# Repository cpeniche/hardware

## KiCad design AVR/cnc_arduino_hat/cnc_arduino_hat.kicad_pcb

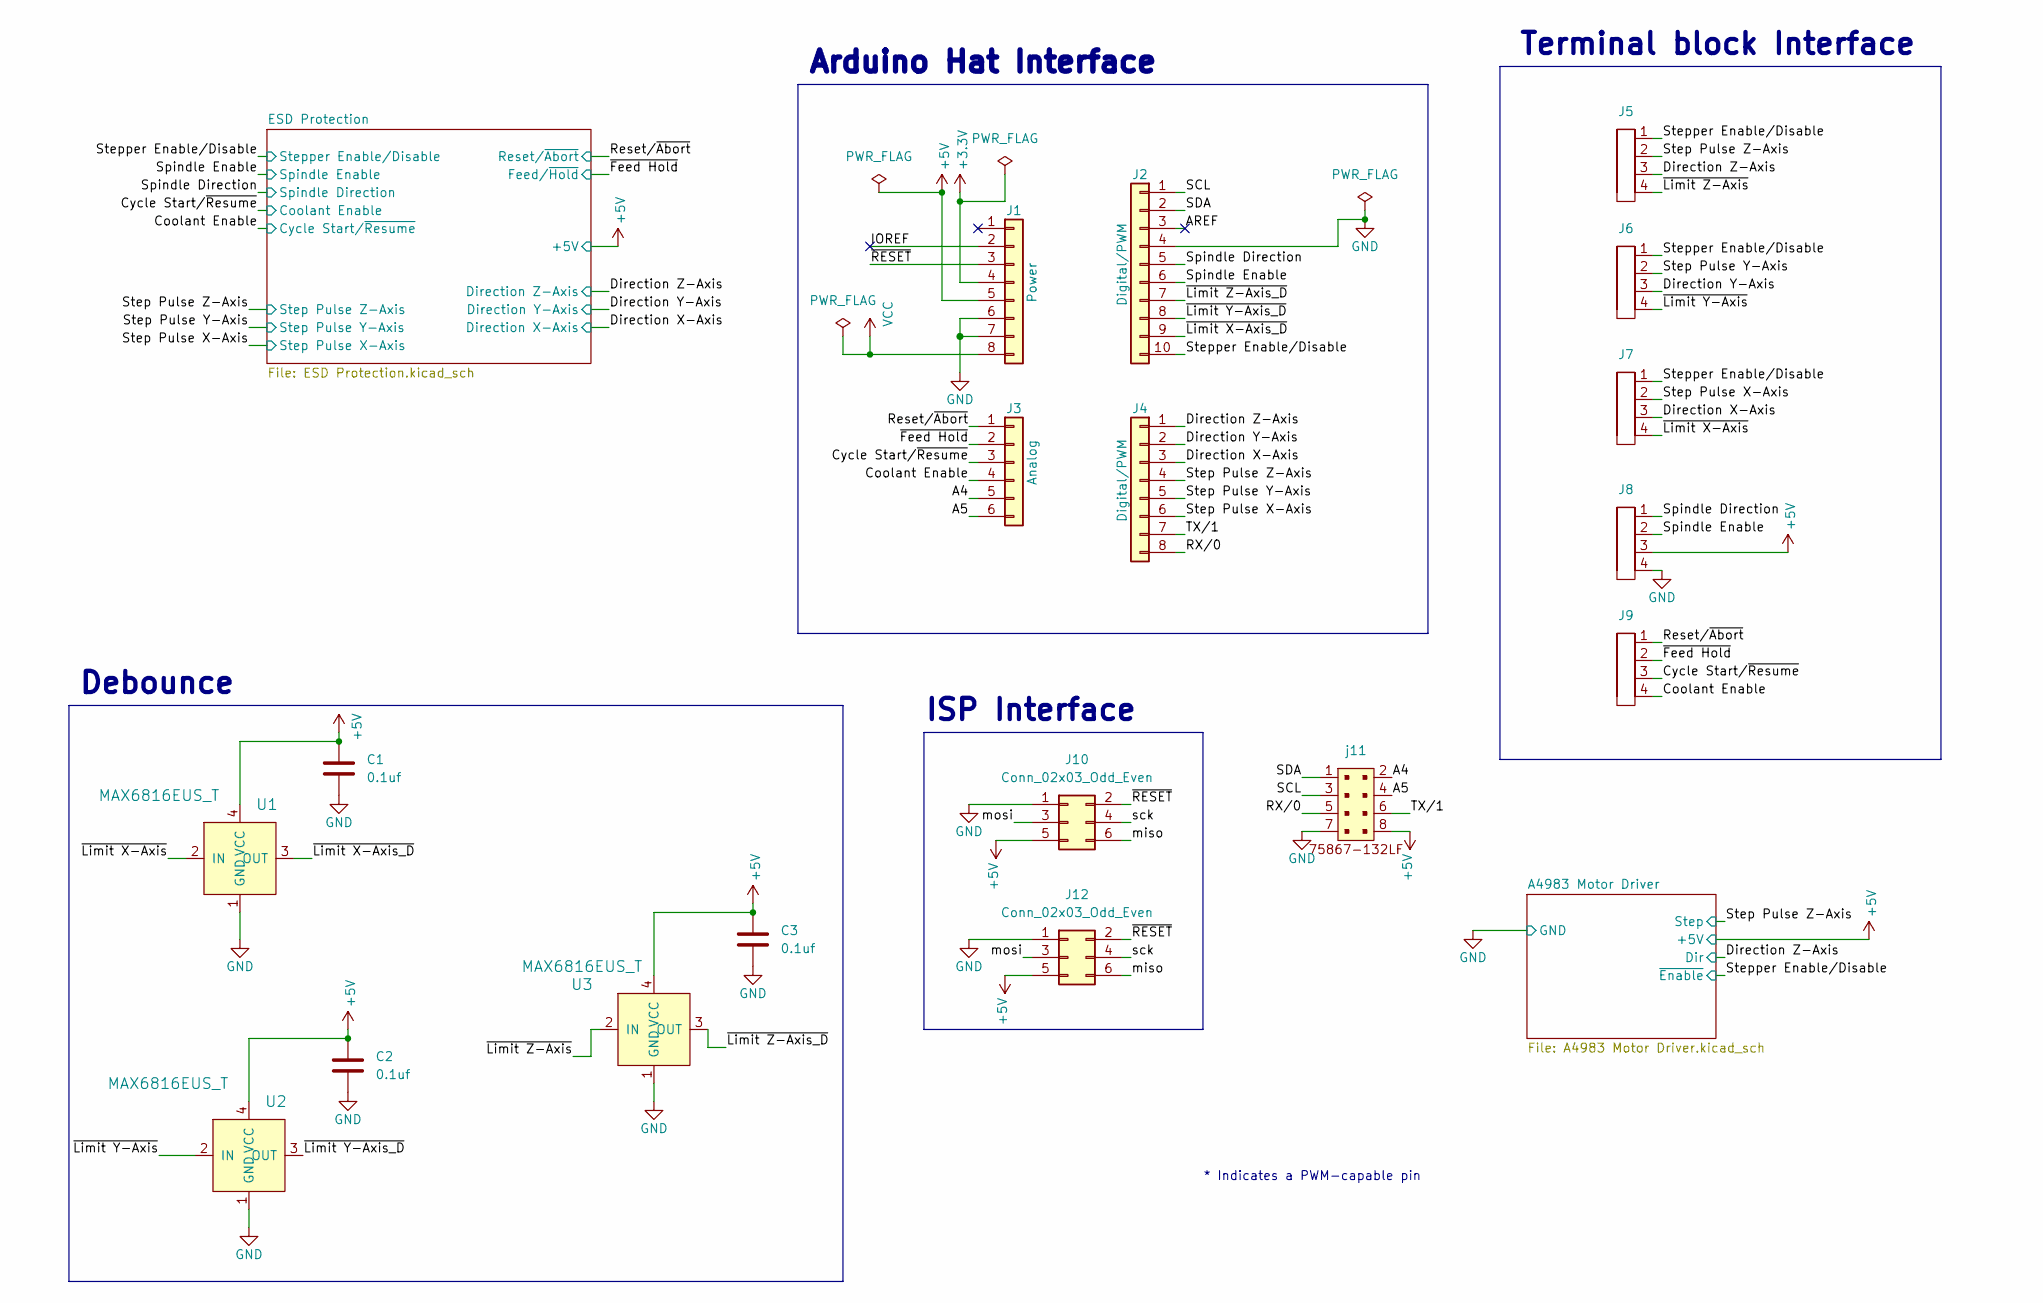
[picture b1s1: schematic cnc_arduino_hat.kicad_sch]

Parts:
C1, C2, C3: 0.1uf; C_0603_1608Metric_Pad1.08x0.95mm_HandSolder
J1: Power; PinHeader_1x08_P2.54mm_Vertical_SMD_Pin1Left
J2: Digital/PWM; PinHeader_1x10_P2.54mm_Vertical_SMD_Pin1Right
J3: Analog; PinHeader_1x06_P2.54mm_Vertical_SMD_Pin1Left
J4: Digital/PWM; PinHeader_1x08_P2.54mm_Vertical_SMD_Pin1Left
J5, J6, J7, J8, J9: Term_Block_1X4_P3.18mm
J10: Conn_02x03_Odd_Even; PinSocket_2x03_P2.54mm_Vertical
J12: Conn_02x03_Odd_Even; PinHeader_2x03_P2.54mm_Vertical
U1, U2, U3: MAX6816EUS_T; SOT-143-4; MPN MAX6816EUS+T; Digi-Key_PN MAX6816EUS+TCT-ND
j11: PinHeader_2x4_P2.54mm_Shrouded

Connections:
+3V3: J1.4
+5V: C1.1, C2.1, C3.1, J1.5, J8.3, J10.5, J12.5, U1.4 (VCC), U2.4 (VCC), U3.4 (VCC), j11.8; also elsewhere on the board
/A4: J3.5, j11.2
/A5: J3.6, j11.4
/AREF: J2.3
/Coolant Enable: J3.4, J9.4; also elsewhere on the board
/Cycle Start/~Resume: J3.3, J9.3; also elsewhere on the board
/Direction X-Axis: J4.3, J7.3; also elsewhere on the board
/Direction Y-Axis: J4.2, J6.3; also elsewhere on the board
/Direction Z-Axis: J4.1, J5.3; also elsewhere on the board
/IOREF: J1.2
/RX/0: J4.8, j11.5
/Reset/~Abort: J3.1, J9.1; also elsewhere on the board
/SCL: J2.1, j11.3
/SDA: J2.2, j11.1
/Spindle Direction: J2.5, J8.1; also elsewhere on the board
/Spindle Enable: J2.6, J8.2; also elsewhere on the board
/Step Pulse X-Axis: J4.6, J7.2; also elsewhere on the board
/Step Pulse Y-Axis: J4.5, J6.2; also elsewhere on the board
/Step Pulse Z-Axis: J4.4, J5.2; also elsewhere on the board
/Stepper Enable/Disable: J2.10, J5.1, J6.1, J7.1; also elsewhere on the board
/TX/1: J4.7, j11.6
/miso: J10.6, J12.6
/mosi: J10.3, J12.3
/sck: J10.4, J12.4
/~Feed Hold: J3.2, J9.2; also elsewhere on the board
/~Limit X-Axis_D: J2.9, U1.3 (OUT)
/~Limit X-Axis: J7.4, U1.2 (IN)
/~Limit Y-Axis_D: J2.8, U2.3 (OUT)
/~Limit Y-Axis: J6.4, U2.2 (IN)
/~Limit Z-Axis_D: J2.7, U3.3 (OUT)
/~Limit Z-Axis: J5.4, U3.2 (IN)
/~RESET: J1.3, J10.2, J12.2
GND: C1.2, C2.2, C3.2, J1.6, J1.7, J2.4, J8.4, J10.1, J12.1, U1.1 (GND), U2.1 (GND), U3.1 (GND), j11.7; also elsewhere on the board
VCC: J1.8

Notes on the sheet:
ISP Interface
Terminal block Interface
Debounce
* Indicates a PWM-capable pin
Arduino Hat Interface

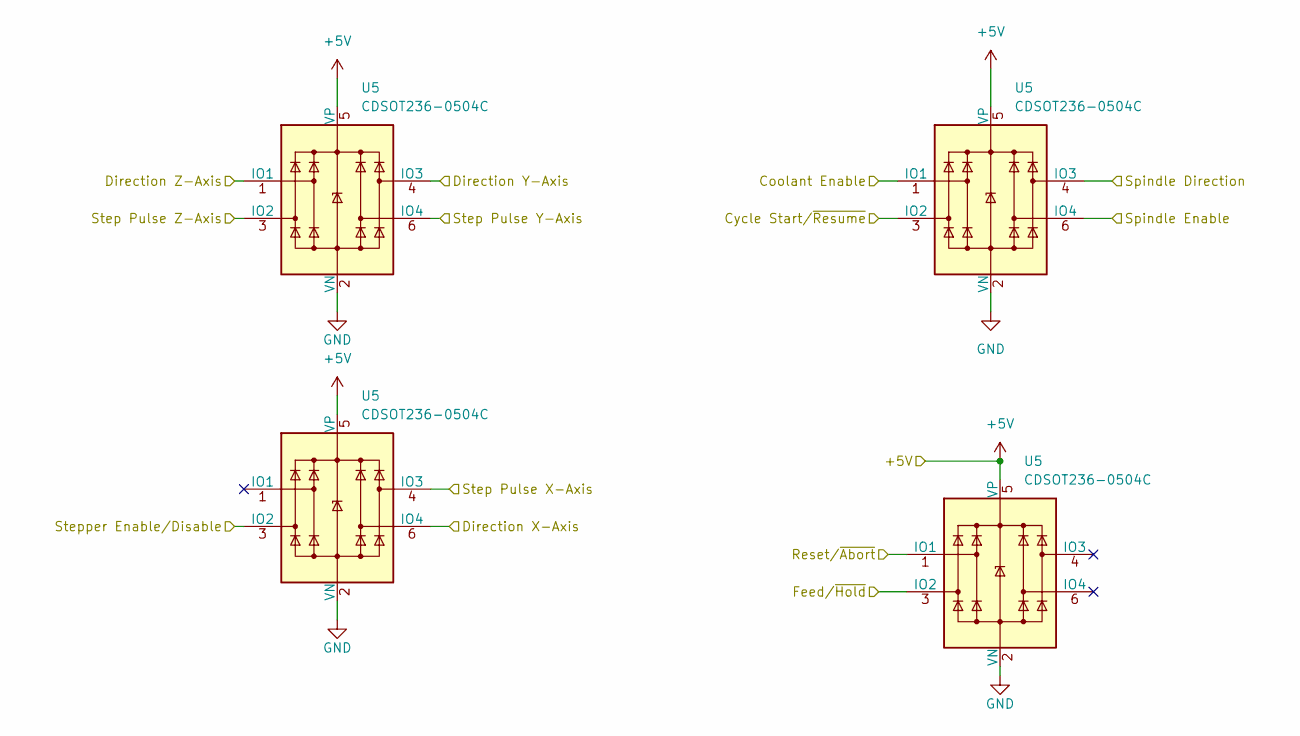
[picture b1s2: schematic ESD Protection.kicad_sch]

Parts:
U5: CDSOT236-0504C; SOT-23-6

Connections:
+5V: U5.5 (VP); also elsewhere on the board
/Direction Y-Axis: U5.4 (IO3); also elsewhere on the board
/Direction Z-Axis: U5.1 (IO1); also elsewhere on the board
/Step Pulse Y-Axis: U5.6 (IO4); also elsewhere on the board
/Step Pulse Z-Axis: U5.3 (IO2); also elsewhere on the board
GND: U5.2 (VN); also elsewhere on the board

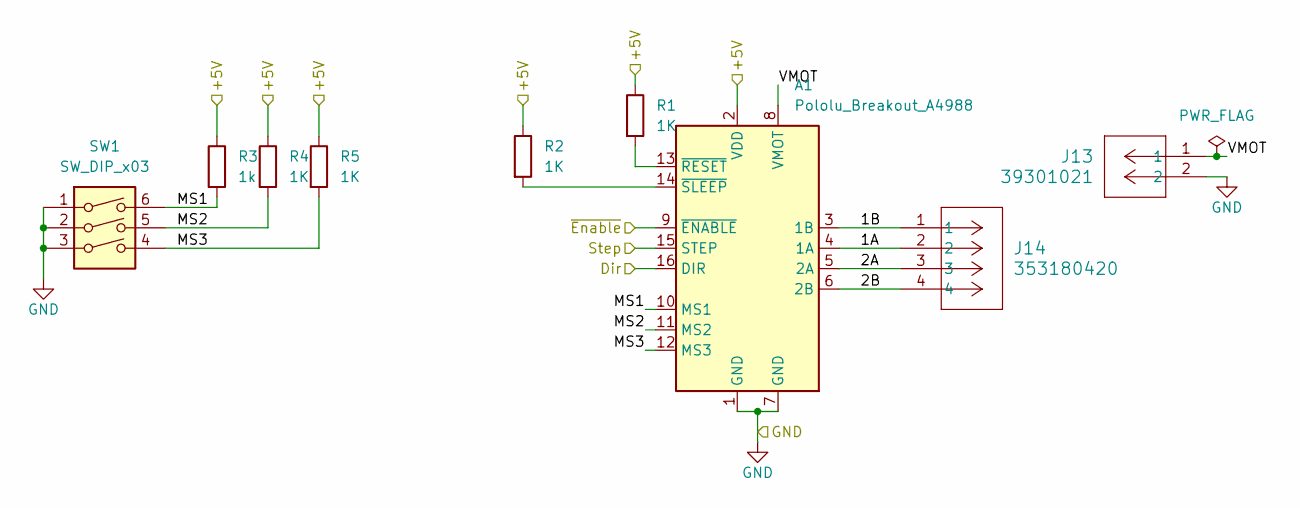
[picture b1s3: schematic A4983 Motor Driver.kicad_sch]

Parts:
A1: Pololu_Breakout_A4988; Pololu_Breakout-16_15.2x20.3mm
J13: 39301021; CON_39301021
J14: 353180420; CONN_35318-0420_MOL
R1, R2, R4, R5: 1K; R_0805_2012Metric_Pad1.20x1.40mm_HandSolder
R3: 1k; R_0805_2012Metric_Pad1.20x1.40mm_HandSolder
SW1: SW_DIP_x03; SW_DIP_SPSTx03_Slide_9.78x9.8mm_W8.61mm_P2.54mm

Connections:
+5V: A1.2 (VDD), R1.1, R2.1, R3.1, R4.1, R5.1; also elsewhere on the board
/A4983 Motor Driver/1A: A1.4 (1A), J14.2
/A4983 Motor Driver/1B: A1.3 (1B), J14.1
/A4983 Motor Driver/2A: A1.5 (2A), J14.3
/A4983 Motor Driver/2B: A1.6 (2B), J14.4
/A4983 Motor Driver/MS1: A1.10 (MS1), R3.2, SW1.6
/A4983 Motor Driver/MS2: A1.11 (MS2), R4.2, SW1.5
/A4983 Motor Driver/MS3: A1.12 (MS3), R5.2, SW1.4
/A4983 Motor Driver/VMOT: A1.8 (VMOT), J13.1
/Direction Z-Axis: A1.16 (DIR); also elsewhere on the board
/Step Pulse Z-Axis: A1.15 (STEP); also elsewhere on the board
/Stepper Enable/Disable: A1.9 (~ENABLE); also elsewhere on the board
GND: A1.1 (GND), A1.7 (GND), J13.2, SW1.1, SW1.2, SW1.3; also elsewhere on the board
unnamed: A1.13 (~RESET), R1.2
unnamed: A1.14 (~SLEEP), R2.2

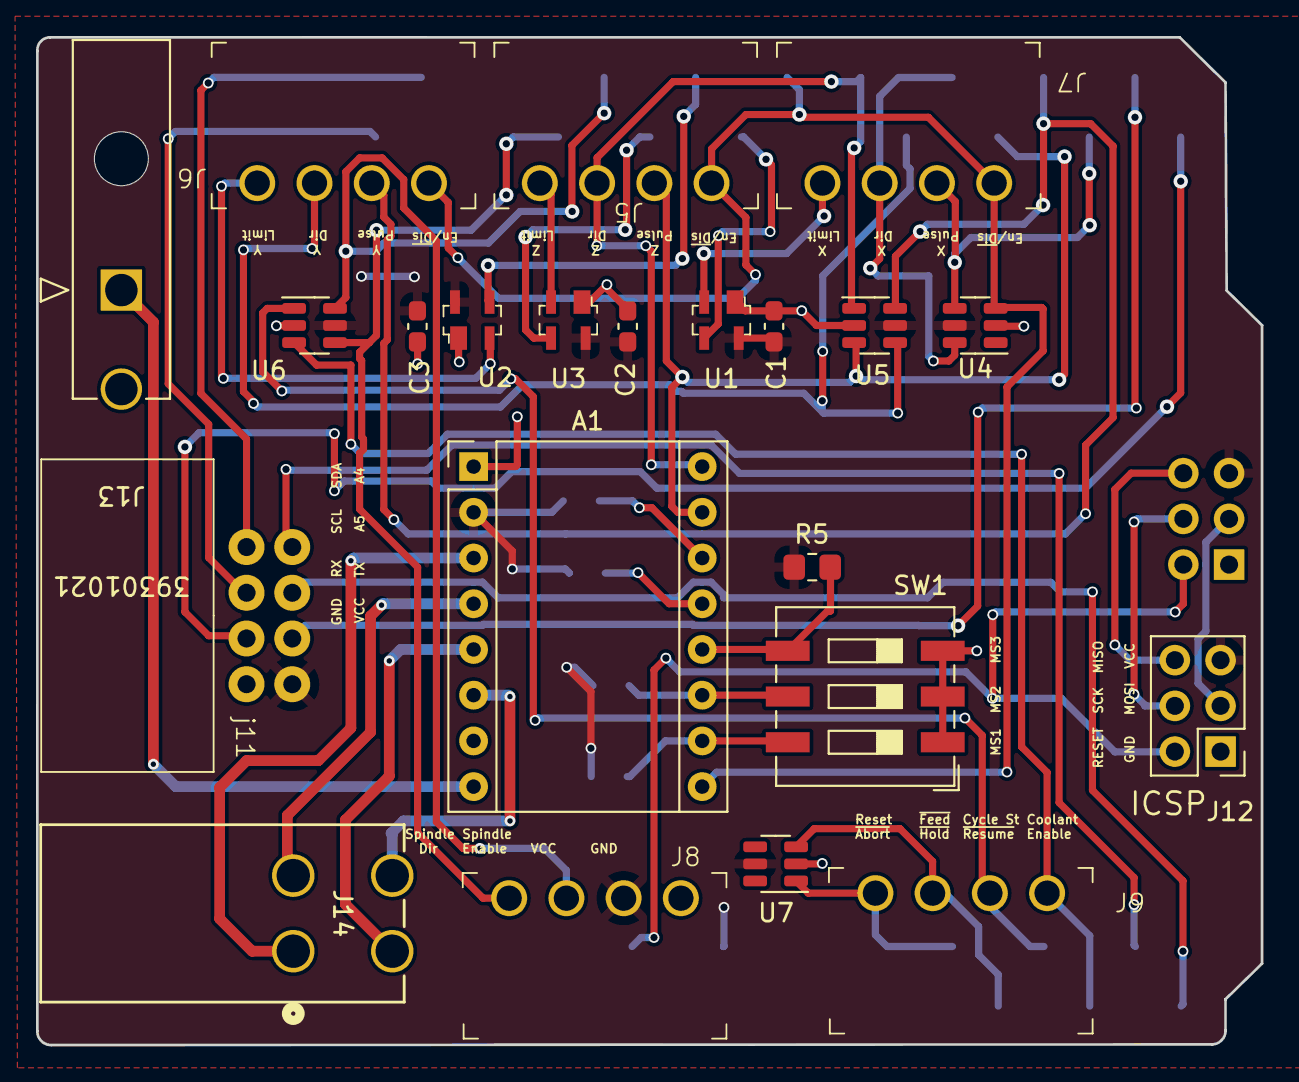
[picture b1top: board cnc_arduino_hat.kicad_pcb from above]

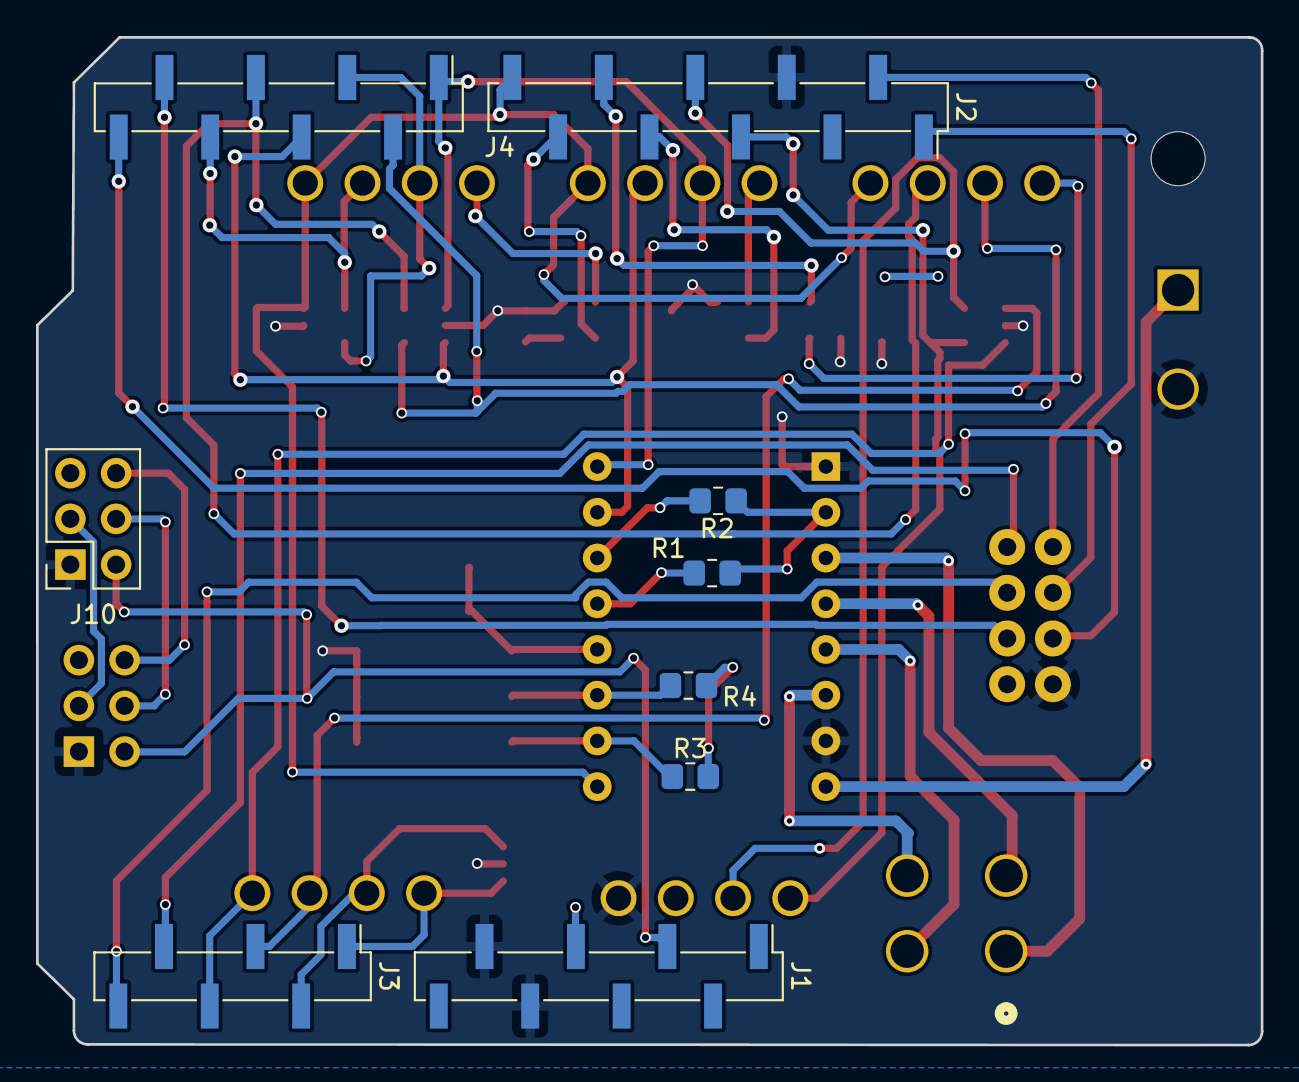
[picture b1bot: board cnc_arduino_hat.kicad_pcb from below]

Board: 2 copper layers, 68.0 x 56.0 mm, 31 parts (9 on the bottom side), 41 nets.

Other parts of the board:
U4, U6, U7: CDSOT236-0504C; SOT-23-6

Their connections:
+5V: U4.5 (VP), U6.5 (VP), U7.5 (VP); also elsewhere on the board
/Coolant Enable: U6.3 (IO2); also elsewhere on the board
/Cycle Start/~Resume: U6.1 (IO1); also elsewhere on the board
/Direction X-Axis: U4.6 (IO4); also elsewhere on the board
/Reset/~Abort: U7.1 (IO1); also elsewhere on the board
/Spindle Direction: U6.4 (IO3); also elsewhere on the board
/Spindle Enable: U6.6 (IO4); also elsewhere on the board
/Step Pulse X-Axis: U4.4 (IO3); also elsewhere on the board
/Stepper Enable/Disable: U4.3 (IO2); also elsewhere on the board
/~Feed Hold: U7.3 (IO2); also elsewhere on the board
GND: U4.2 (VN), U6.2 (VN), U7.2 (VN); also elsewhere on the board

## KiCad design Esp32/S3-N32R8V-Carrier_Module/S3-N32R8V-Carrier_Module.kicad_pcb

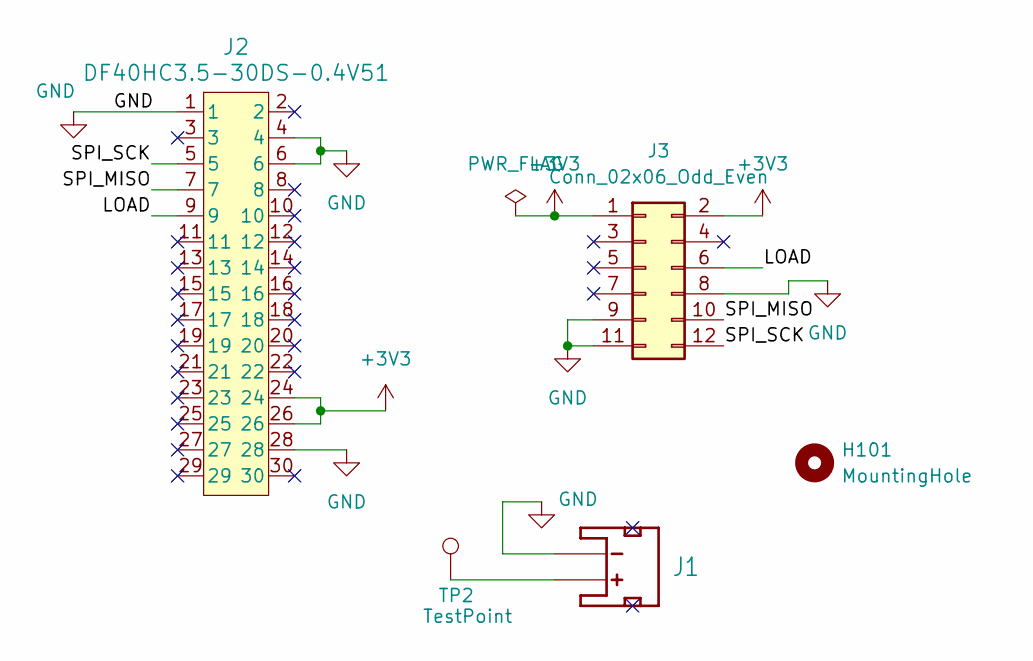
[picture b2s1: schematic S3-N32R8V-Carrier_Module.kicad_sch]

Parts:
H101: MountingHole; MountingHole_2.7mm
J1: JST_PH_S2B-PH-SM4-TB_1x02-1MP_P2.00mm_Horizontal
J2: DF40HC3.5-30DS-0.4V51; CONN_DF40HC3.5-30DS-0.4V51_HIR
J3: Conn_02x06_Odd_Even; PinHeader_2x06_P2.54mm_Vertical_SMD
TP2: TestPoint; TestPoint_Pad_1.0x1.0mm

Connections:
+3V3: J2.24, J2.26, J3.1, J3.2
/LOAD: J2.9, J3.6
/SPI_MISO: J2.7, J3.10
/SPI_SCK: J2.5, J3.12
GND: J1.1 (-), J2.1, J2.4, J2.6, J2.28, J3.8, J3.9, J3.11
unnamed: J1.2 (+), TP2.1

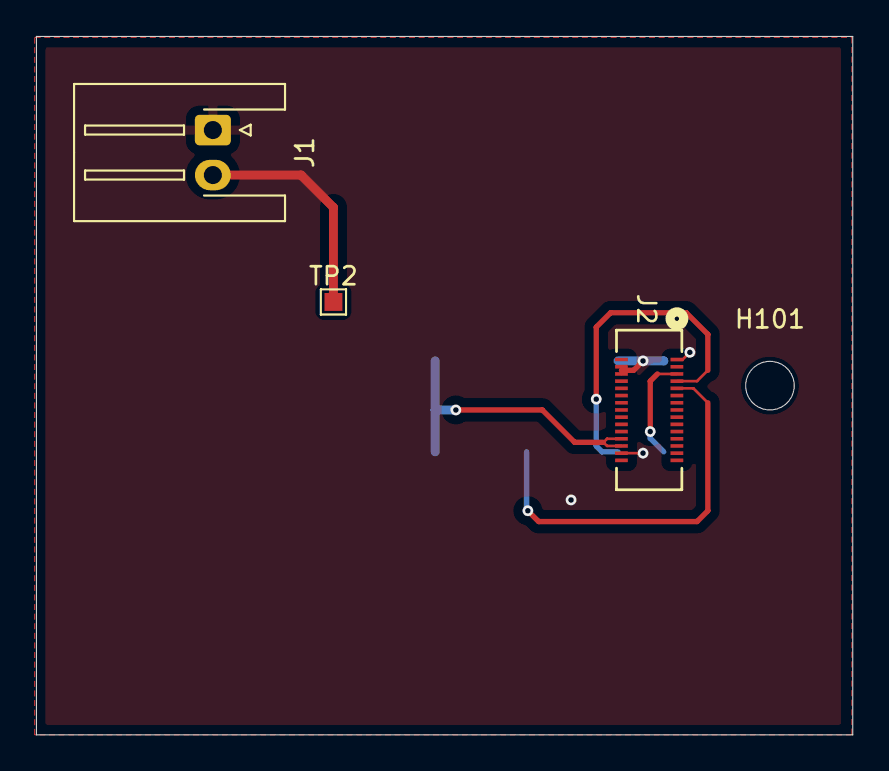
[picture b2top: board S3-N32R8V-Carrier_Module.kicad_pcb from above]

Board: 2 copper layers, 45.3 x 38.8 mm, 5 parts (1 on the bottom side), 6 nets.

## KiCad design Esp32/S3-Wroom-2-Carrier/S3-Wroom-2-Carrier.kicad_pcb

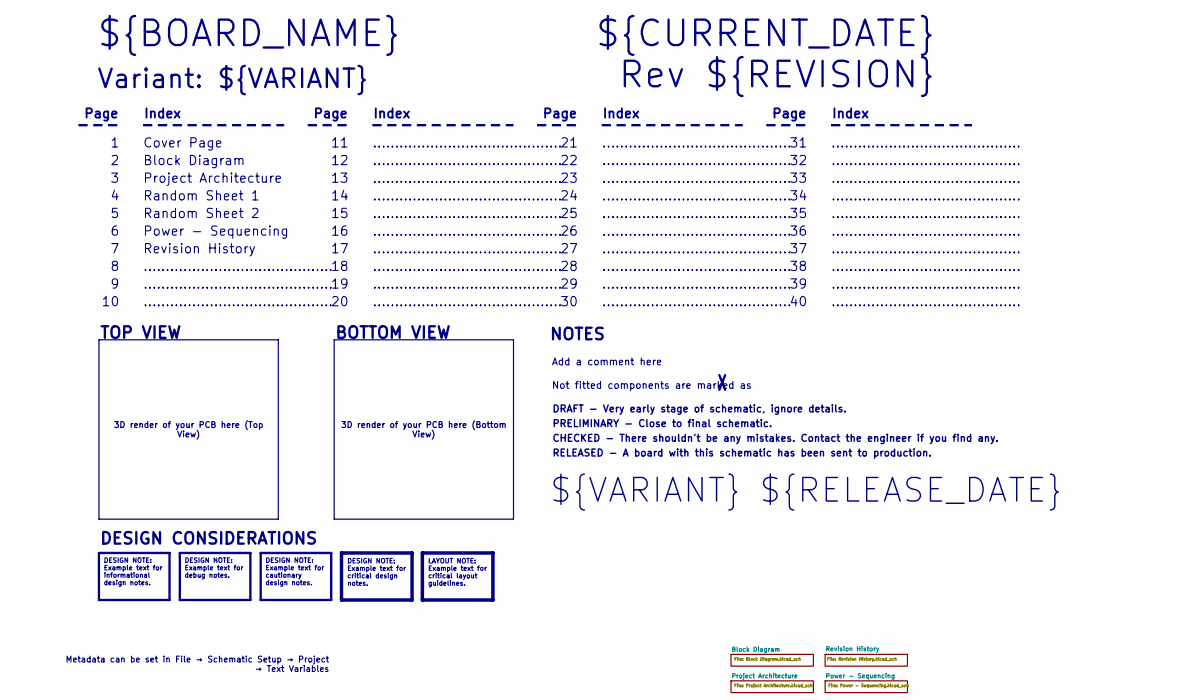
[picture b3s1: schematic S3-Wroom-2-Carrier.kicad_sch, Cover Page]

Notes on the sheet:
BOTTOM VIEW
...........................................
RELEASED - A board with this schematic has been sent to production.
Page
TOP VIEW
Not fitted components are marked as
Index
PRELIMINARY - Close to final schematic.
${VARIANT} ${RELEASE_DATE}
Random Sheet 1
${CURRENT_DATE}
Variant: ${VARIANT}
Rev ${REVISION}
Random Sheet 2
${BOARD_NAME}
DRAFT - Very early stage of schematic, ignore details.
Power - Sequencing
Block Diagram
Add a comment here
Cover Page
NOTES
Project Architecture
CHECKED - There shouldn't be any mistakes. Contact the engineer if you find any.
DESIGN CONSIDERATIONS
Revision History
3D render of your PCB here (Bottom View)
3D render of your PCB here (Top View)
Metadata can be set in File → Schematic Setup → Project → Text Variables
DESIGN NOTE: Example text for informational design notes.
LAYOUT NOTE: Example text for critical layout guidelines.
DESIGN NOTE: Example text for cautionary design notes.
DESIGN NOTE: Example text for debug notes.
DESIGN NOTE: Example text for critical design notes.

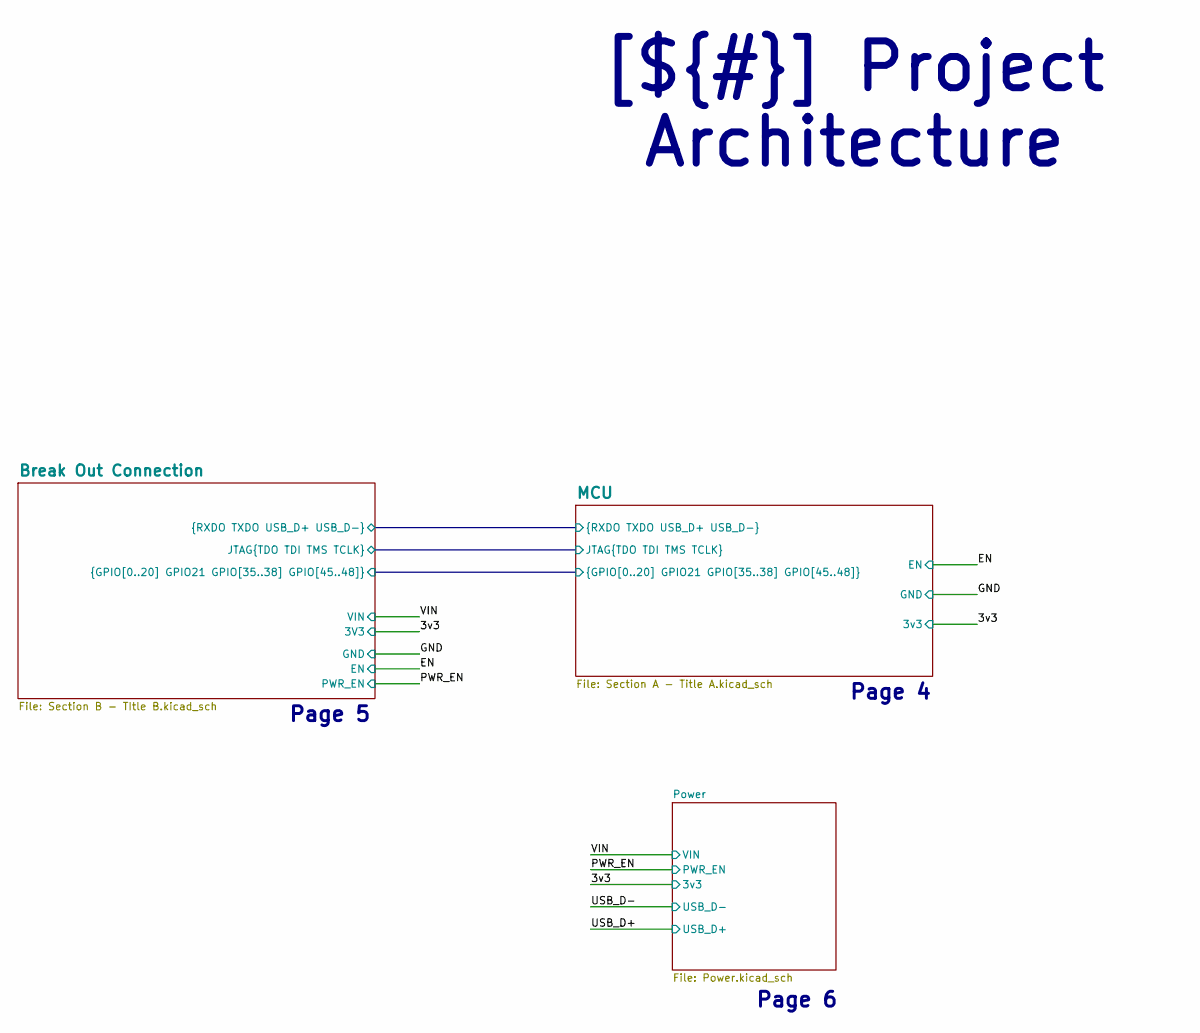
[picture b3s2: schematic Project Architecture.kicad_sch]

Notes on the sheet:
Page 6
Page 4
Page 5
[${#}] ${TITLE}

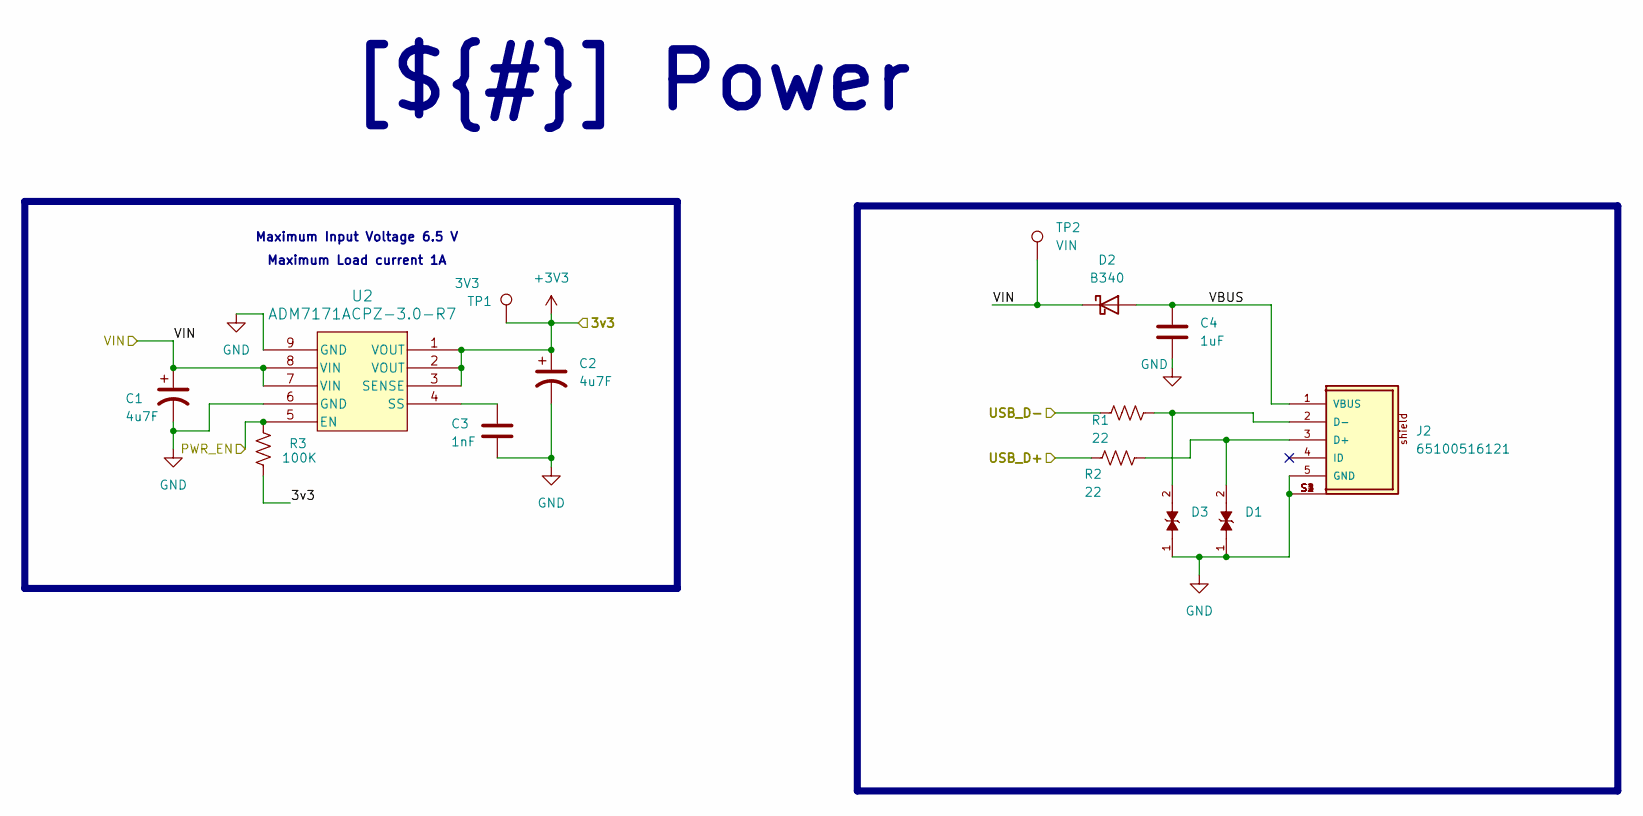
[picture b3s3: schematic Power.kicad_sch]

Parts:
C1, C2: 4u7F; C_0805_2012Metric_Pad1.18x1.45mm_HandSolder
C3: 1nF; C_0805_2012Metric_Pad1.18x1.45mm_HandSolder
C4: 1uF; C_0805_2012Metric_Pad1.18x1.45mm_HandSolder
D1, D3: DIOC1608X36N
D2: B340; D_SMA
J2: 65100516121; Usb_B_mini_Wurth_65100516121
R1, R2: 22; R_0805_2012Metric_Pad1.20x1.40mm_HandSolder
R3: 100K; R_0805_2012Metric_Pad1.20x1.40mm_HandSolder
TP1: 3V3; TestPoint_Pad_1.0x1.0mm
TP2: VIN; TestPoint_Pad_1.0x1.0mm
U2: ADM7171ACPZ-3.0-R7; LFCSP-8-1EP_3x3mm_P0.5mm_EP_1.70x2.54mm

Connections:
+3V3: C2.1, R3.2, TP1.1, U2.1 (VOUT), U2.2 (VOUT), U2.3 (SENSE); also elsewhere on the board
/Project Architecture/Break Out Connection/USB_D+: R2.1; also elsewhere on the board
/Project Architecture/Break Out Connection/USB_D-: R1.1; also elsewhere on the board
/Project Architecture/PWR_EN: R3.1, U2.5 (EN); also elsewhere on the board
/Project Architecture/Power/VBUS: C4.1, D2.2 (A), J2.1 (VBUS)
/Project Architecture/VIN: C1.1, D2.1 (K), TP2.1, U2.7 (VIN), U2.8 (VIN); also elsewhere on the board
GND: C1.2, C2.2, C3.2, C4.2, D1.1, D3.1, J2.5 (GND), J2.S1, J2.S2, J2.S3, J2.S4, U2.6 (GND), U2.9 (GND); also elsewhere on the board
unnamed: D1.2, J2.3 (D+), R2.2
unnamed: D3.2, J2.2 (D-), R1.2
unnamed: C3.1, U2.4 (SS)

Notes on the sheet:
Maximum Load current 1A
Maximum Input Voltage 6.5 V
[${#}] ${TITLE}

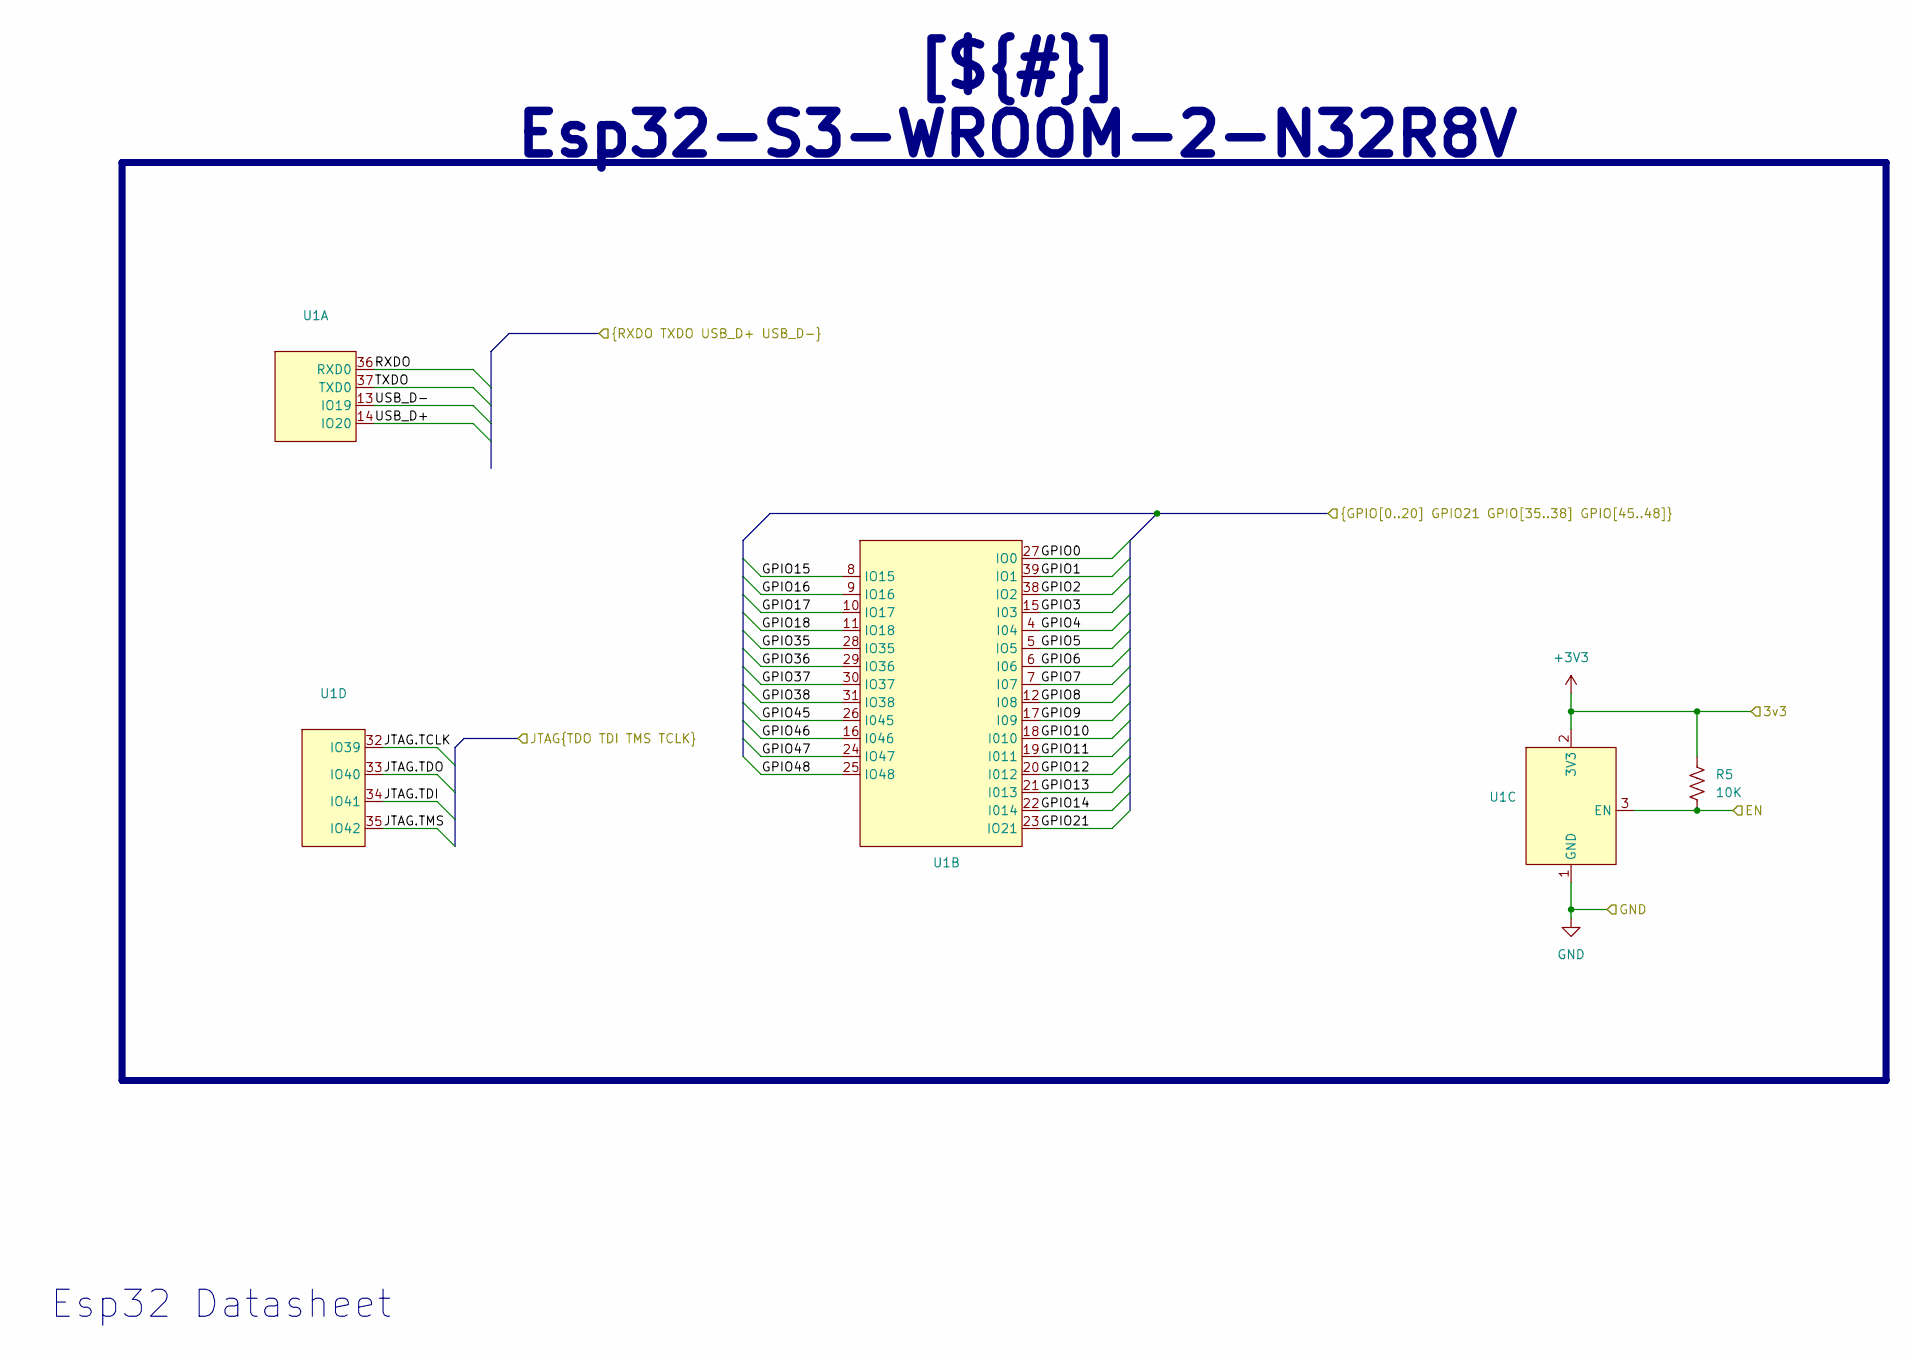
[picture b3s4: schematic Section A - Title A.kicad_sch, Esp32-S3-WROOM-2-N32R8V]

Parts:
R5: 10K; R_0805_2012Metric_Pad1.20x1.40mm_HandSolder
U1: ESP32-S3-WROOM-2

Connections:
+3V3: R5.1, U1.2 (3V3); also elsewhere on the board
/Project Architecture/Break Out Connection/GPIO0: U1.27 (IO0); also elsewhere on the board
/Project Architecture/Break Out Connection/GPIO1: U1.39 (IO1); also elsewhere on the board
/Project Architecture/Break Out Connection/GPIO2: U1.38 (IO2); also elsewhere on the board
/Project Architecture/Break Out Connection/GPIO3: U1.15 (I03); also elsewhere on the board
/Project Architecture/Break Out Connection/GPIO4: U1.4 (I04); also elsewhere on the board
/Project Architecture/Break Out Connection/GPIO5: U1.5 (IO5); also elsewhere on the board
/Project Architecture/Break Out Connection/GPIO6: U1.6 (I06); also elsewhere on the board
/Project Architecture/Break Out Connection/GPIO7: U1.7 (I07); also elsewhere on the board
/Project Architecture/Break Out Connection/GPIO8: U1.12 (I08); also elsewhere on the board
/Project Architecture/Break Out Connection/GPIO9: U1.17 (I09); also elsewhere on the board
/Project Architecture/Break Out Connection/GPIO10: U1.18 (I010); also elsewhere on the board
/Project Architecture/Break Out Connection/GPIO11: U1.19 (I011); also elsewhere on the board
/Project Architecture/Break Out Connection/GPIO12: U1.20 (I012); also elsewhere on the board
/Project Architecture/Break Out Connection/GPIO13: U1.21 (I013); also elsewhere on the board
/Project Architecture/Break Out Connection/GPIO14: U1.22 (I014); also elsewhere on the board
/Project Architecture/Break Out Connection/GPIO15: U1.8 (IO15); also elsewhere on the board
/Project Architecture/Break Out Connection/GPIO16: U1.9 (IO16); also elsewhere on the board
/Project Architecture/Break Out Connection/GPIO17: U1.10 (IO17); also elsewhere on the board
/Project Architecture/Break Out Connection/GPIO18: U1.11 (IO18); also elsewhere on the board
/Project Architecture/Break Out Connection/GPIO21: U1.23 (IO21); also elsewhere on the board
/Project Architecture/Break Out Connection/GPIO35: U1.28 (IO35); also elsewhere on the board
/Project Architecture/Break Out Connection/GPIO36: U1.29 (IO36); also elsewhere on the board
/Project Architecture/Break Out Connection/GPIO37: U1.30 (IO37); also elsewhere on the board
/Project Architecture/Break Out Connection/GPIO38: U1.31 (IO38); also elsewhere on the board
/Project Architecture/Break Out Connection/GPIO45: U1.26 (I045); also elsewhere on the board
/Project Architecture/Break Out Connection/GPIO46: U1.16 (I046); also elsewhere on the board
/Project Architecture/Break Out Connection/GPIO47: U1.24 (IO47); also elsewhere on the board
/Project Architecture/Break Out Connection/GPIO48: U1.25 (IO48); also elsewhere on the board
/Project Architecture/Break Out Connection/JTAG.TCLK: U1.32 (IO39); also elsewhere on the board
/Project Architecture/Break Out Connection/JTAG.TDI: U1.34 (IO41); also elsewhere on the board
/Project Architecture/Break Out Connection/JTAG.TDO: U1.33 (IO40); also elsewhere on the board
/Project Architecture/Break Out Connection/JTAG.TMS: U1.35 (IO42); also elsewhere on the board
/Project Architecture/Break Out Connection/RXDO: U1.36 (RXD0); also elsewhere on the board
/Project Architecture/Break Out Connection/TXDO: U1.37 (TXD0); also elsewhere on the board
/Project Architecture/Break Out Connection/USB_D+: U1.14 (IO20); also elsewhere on the board
/Project Architecture/Break Out Connection/USB_D-: U1.13 (IO19); also elsewhere on the board
/Project Architecture/EN: R5.2, U1.3 (EN); also elsewhere on the board
GND: U1.1 (GND), U1.40 (GND), U1.41 (GND); also elsewhere on the board

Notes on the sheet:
Esp32 Datasheet
[${#}] ${TITLE}

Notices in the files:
parts and their libraries:
Released under the Creative Commons Attribution Share-Alike 4.0 License
https://creativecommons.org/licenses/by-sa/4.0
